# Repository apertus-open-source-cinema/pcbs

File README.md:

# apertus pcbs
This generates artefacts (gerbers, etc.) for the eagle based PCBs of the apertus project. 
Currently it generates
- a zip with gerbers for the [4 layer oshpark process](https://docs.oshpark.com/services/four-layer/)
- (searchable) PDFs of the schematic
- preview images of the boards
- a [webpage](https://apertus-open-source-cinema.github.io/pcbs) that displays these artefacts grouped by board versions and variants
## Process
Generating these artefacts is a multi step process. First the board and schematic files located in the `boards` folder are analyzed to determine license and copyright information from the silkscreen and schematic annotations. This will generate `.license` files for each board and schematic file that does not already have one. To run this steps use 
```sh
python3 analyze.py
```
Please check the extracted information for correctness and fix any errors found before commiting the `.license` file.

The next step of the process is the collection of all the PCB versions, variants and assembly variants. This is done by running
``` sh
python3 generate_info.py
```
This creates `info.json` containing all the infos.

Now the gerbers, schematic PDFs and preview images are generated. For this step EAGLE version 7 needs to be installed. Running
``` sh
python3 gen.py
```
will then generate them. This can take very long depending on the number of cpu cores.

Finally the webpage displaying and providing download links can be generated. For this the preview first images need to be converted from PNG to WebP. This can for example be done with

``` sh
find boards -name '*.png' | parallel -j100% cwebp -lossless {} -o {.}.webp
```

Then the webpage can be built:
``` sh
cd web && npm run build
```
Note that this will generate a webpage for deployment at https://apertus-open-source-cinema.github.io/pcbs/. For local development you can use
``` sh
cd web && npm install && parcel serve src/index.html
```
## CI setup
The CI does almost the same steps as described above. It uses a docker container generated using
``` sh
$(nix-build --no-out-link docker_image.nix) | docker load
```
to run the steps depending on eagle and furthermore uses `xvfb-run` to avoid the need of an actual X11 server.

Finally it splits the `gen.py` step into multiple shards that are run in parallel across multiple workers, as a single worker can not finish under the `6h` time limit.
## Adding PCBs
To add a new PCB simply drop the pair of `.sch` and `.brd` files in the `boards` folder followed by running 
```sh 
python analyze.py
```
and fixing / manually adding the `.license` files.

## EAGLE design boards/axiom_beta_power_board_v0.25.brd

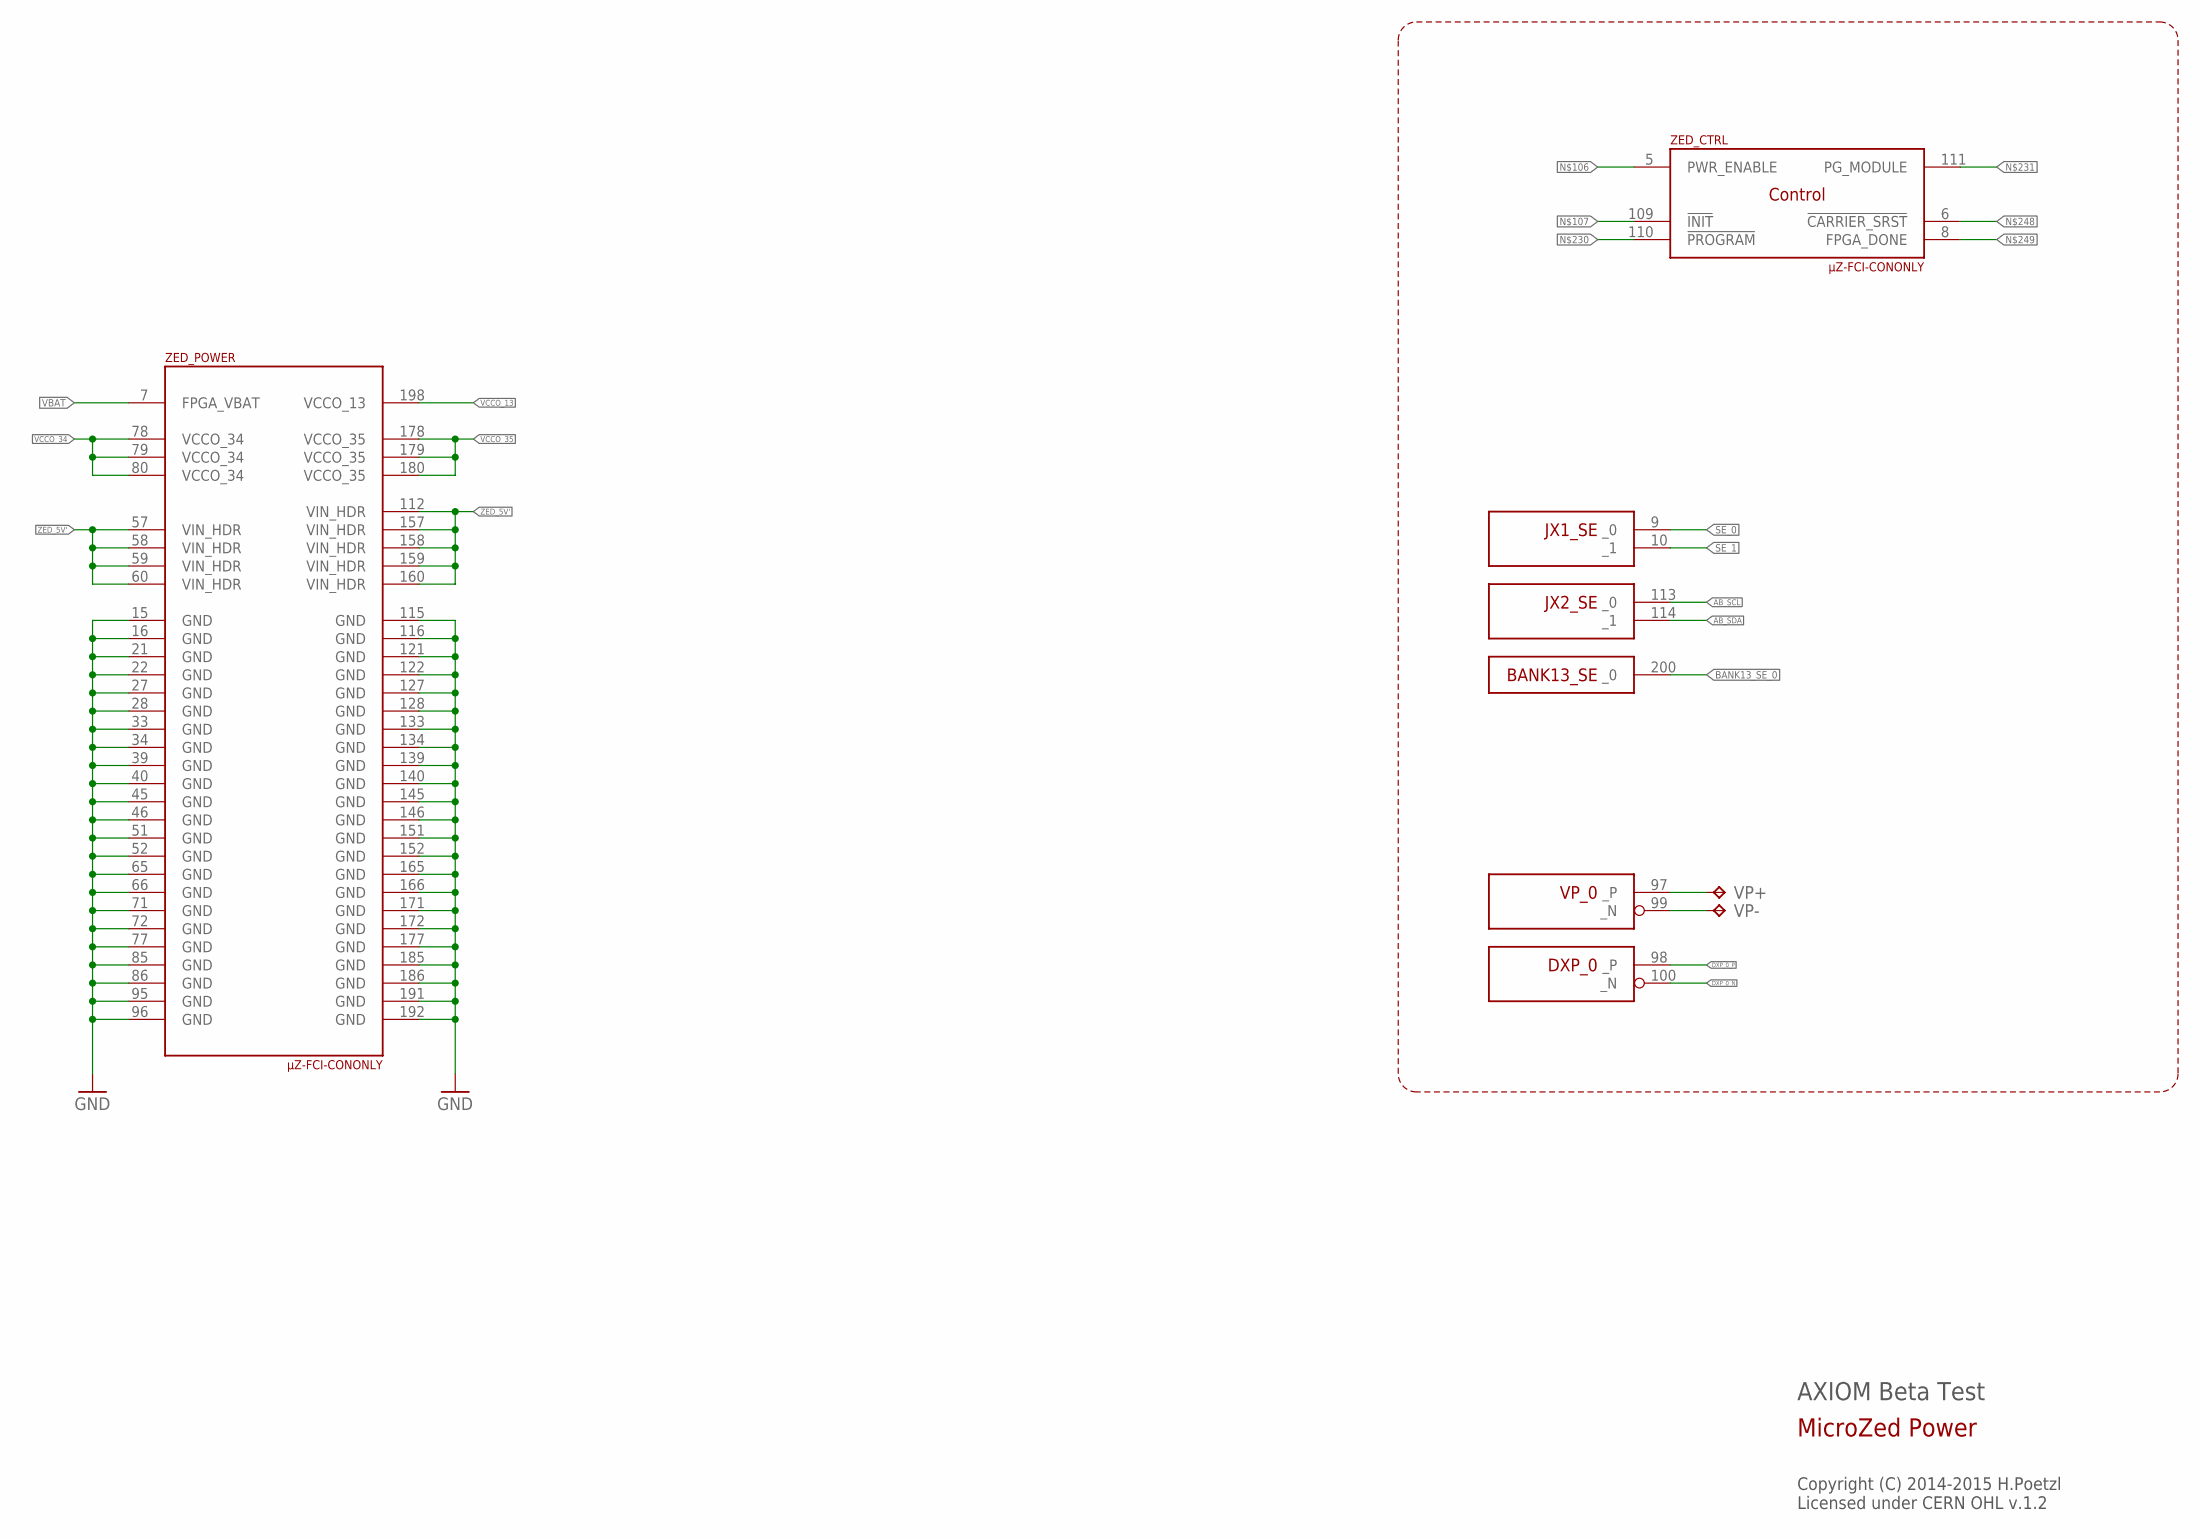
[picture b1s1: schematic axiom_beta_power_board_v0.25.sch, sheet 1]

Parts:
VP+: TPTP16SQ; TP16SQ
VP-: TPTP16SQ; TP16SQ
ZED: µZ-FCI-CONONLY; µZ-CONONLY

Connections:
AB_SCL: ZED.113 (_0); also elsewhere on the board
AB_SDA: ZED.114 (_1); also elsewhere on the board
BANK13_SE_0: ZED.200 (_0); also elsewhere on the board
DXP_0_N: ZED.100 (_N)
DXP_0_P: ZED.98 (_P)
GND: ZED.15 (GND), ZED.16 (GND), ZED.21 (GND), ZED.22 (GND), ZED.27 (GND), ZED.28 (GND), ZED.33 (GND), ZED.34 (GND), ZED.39 (GND), ZED.40 (GND), ZED.45 (GND), ZED.46 (GND), ZED.51 (GND), ZED.52 (GND), ZED.65 (GND), ZED.66 (GND), ZED.71 (GND), ZED.72 (GND), ZED.77 (GND), ZED.85 (GND), ZED.86 (GND), ZED.95 (GND), ZED.96 (GND), ZED.115 (GND), ZED.116 (GND), ZED.121 (GND), ZED.122 (GND), ZED.127 (GND), ZED.128 (GND), ZED.133 (GND), ZED.134 (GND), ZED.139 (GND), ZED.140 (GND), ZED.145 (GND), ZED.146 (GND), ZED.151 (GND), ZED.152 (GND), ZED.165 (GND), ZED.166 (GND), ZED.171 (GND), ZED.172 (GND), ZED.177 (GND), ZED.185 (GND), ZED.186 (GND), ZED.191 (GND), ZED.192 (GND); also elsewhere on the board
SE_0: ZED.9 (_0); also elsewhere on the board
SE_1: ZED.10 (_1); also elsewhere on the board
VBAT: ZED.7 (FPGA_VBAT)
VCCO_13: ZED.198 (VCCO_13); also elsewhere on the board
VCCO_34: ZED.78 (VCCO_34), ZED.79 (VCCO_34), ZED.80 (VCCO_34); also elsewhere on the board
VCCO_35: ZED.178 (VCCO_35), ZED.179 (VCCO_35), ZED.180 (VCCO_35); also elsewhere on the board
VP_0_N: VP-.TP, ZED.99 (_N)
VP_0_P: VP+.TP, ZED.97 (_P)
ZED_5V': ZED.57 (VIN_HDR), ZED.58 (VIN_HDR), ZED.59 (VIN_HDR), ZED.60 (VIN_HDR), ZED.112 (VIN_HDR), ZED.157 (VIN_HDR), ZED.158 (VIN_HDR), ZED.159 (VIN_HDR), ZED.160 (VIN_HDR); also elsewhere on the board

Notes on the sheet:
AXIOM Beta Test
Copyright (C) 2014-2015 H.Poetzl Licensed under CERN OHL v.1.2
MicroZed Power

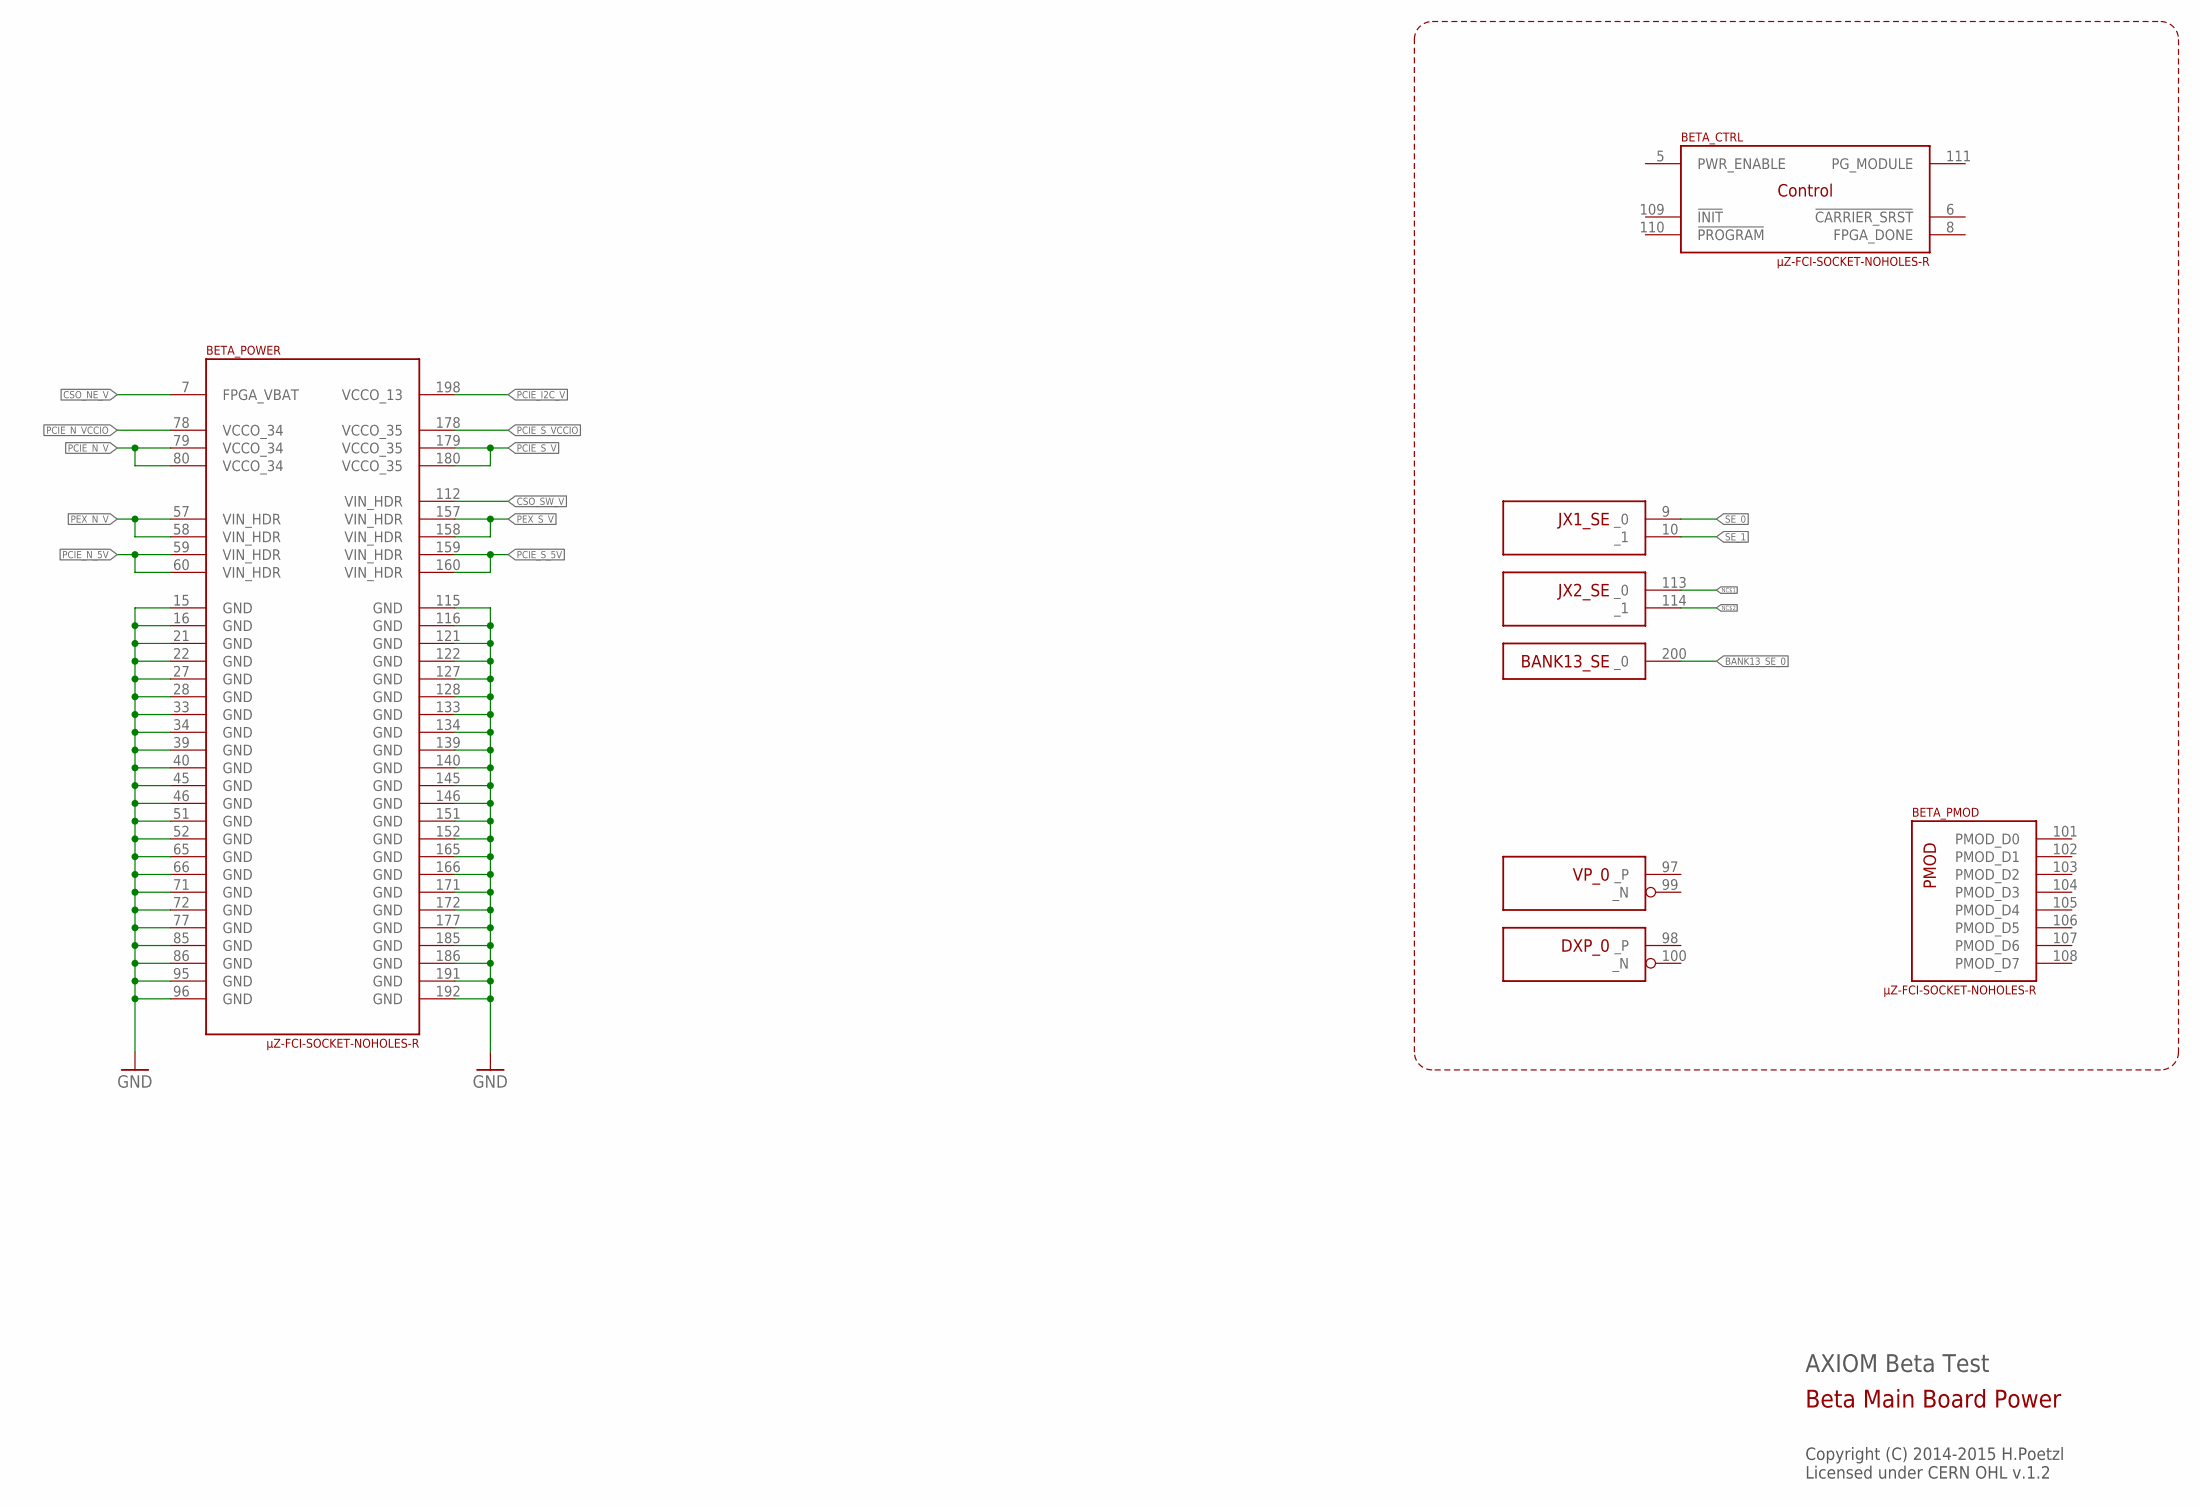
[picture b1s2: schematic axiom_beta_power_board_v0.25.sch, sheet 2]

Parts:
BETA: µZ-FCI-SOCKET-NOHOLES-R; µZ-SOCKET-NOHOLES-R

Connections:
BANK13_SE_0: BETA.200 (_0); also elsewhere on the board
CSO_NE_V: BETA.7 (FPGA_VBAT); also elsewhere on the board
CSO_SW_V: BETA.112 (VIN_HDR); also elsewhere on the board
GND: BETA.15 (GND), BETA.16 (GND), BETA.21 (GND), BETA.22 (GND), BETA.27 (GND), BETA.28 (GND), BETA.33 (GND), BETA.34 (GND), BETA.39 (GND), BETA.40 (GND), BETA.45 (GND), BETA.46 (GND), BETA.51 (GND), BETA.52 (GND), BETA.65 (GND), BETA.66 (GND), BETA.71 (GND), BETA.72 (GND), BETA.77 (GND), BETA.85 (GND), BETA.86 (GND), BETA.95 (GND), BETA.96 (GND), BETA.115 (GND), BETA.116 (GND), BETA.121 (GND), BETA.122 (GND), BETA.127 (GND), BETA.128 (GND), BETA.133 (GND), BETA.134 (GND), BETA.139 (GND), BETA.140 (GND), BETA.145 (GND), BETA.146 (GND), BETA.151 (GND), BETA.152 (GND), BETA.165 (GND), BETA.166 (GND), BETA.171 (GND), BETA.172 (GND), BETA.177 (GND), BETA.185 (GND), BETA.186 (GND), BETA.191 (GND), BETA.192 (GND); also elsewhere on the board
NC$1: BETA.113 (_0)
NC$2: BETA.114 (_1)
PCIE_I2C_V: BETA.198 (VCCO_13)
PCIE_N_5V: BETA.59 (VIN_HDR), BETA.60 (VIN_HDR)
PCIE_N_V: BETA.79 (VCCO_34), BETA.80 (VCCO_34); also elsewhere on the board
PCIE_N_VCCIO: BETA.78 (VCCO_34)
PCIE_S_5V: BETA.159 (VIN_HDR), BETA.160 (VIN_HDR)
PCIE_S_V: BETA.179 (VCCO_35), BETA.180 (VCCO_35); also elsewhere on the board
PCIE_S_VCCIO: BETA.178 (VCCO_35)
PEX_N_V: BETA.57 (VIN_HDR), BETA.58 (VIN_HDR)
PEX_S_V: BETA.157 (VIN_HDR), BETA.158 (VIN_HDR)
SE_0: BETA.9 (_0); also elsewhere on the board
SE_1: BETA.10 (_1); also elsewhere on the board

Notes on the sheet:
AXIOM Beta Test
Copyright (C) 2014-2015 H.Poetzl Licensed under CERN OHL v.1.2
Beta Main Board Power

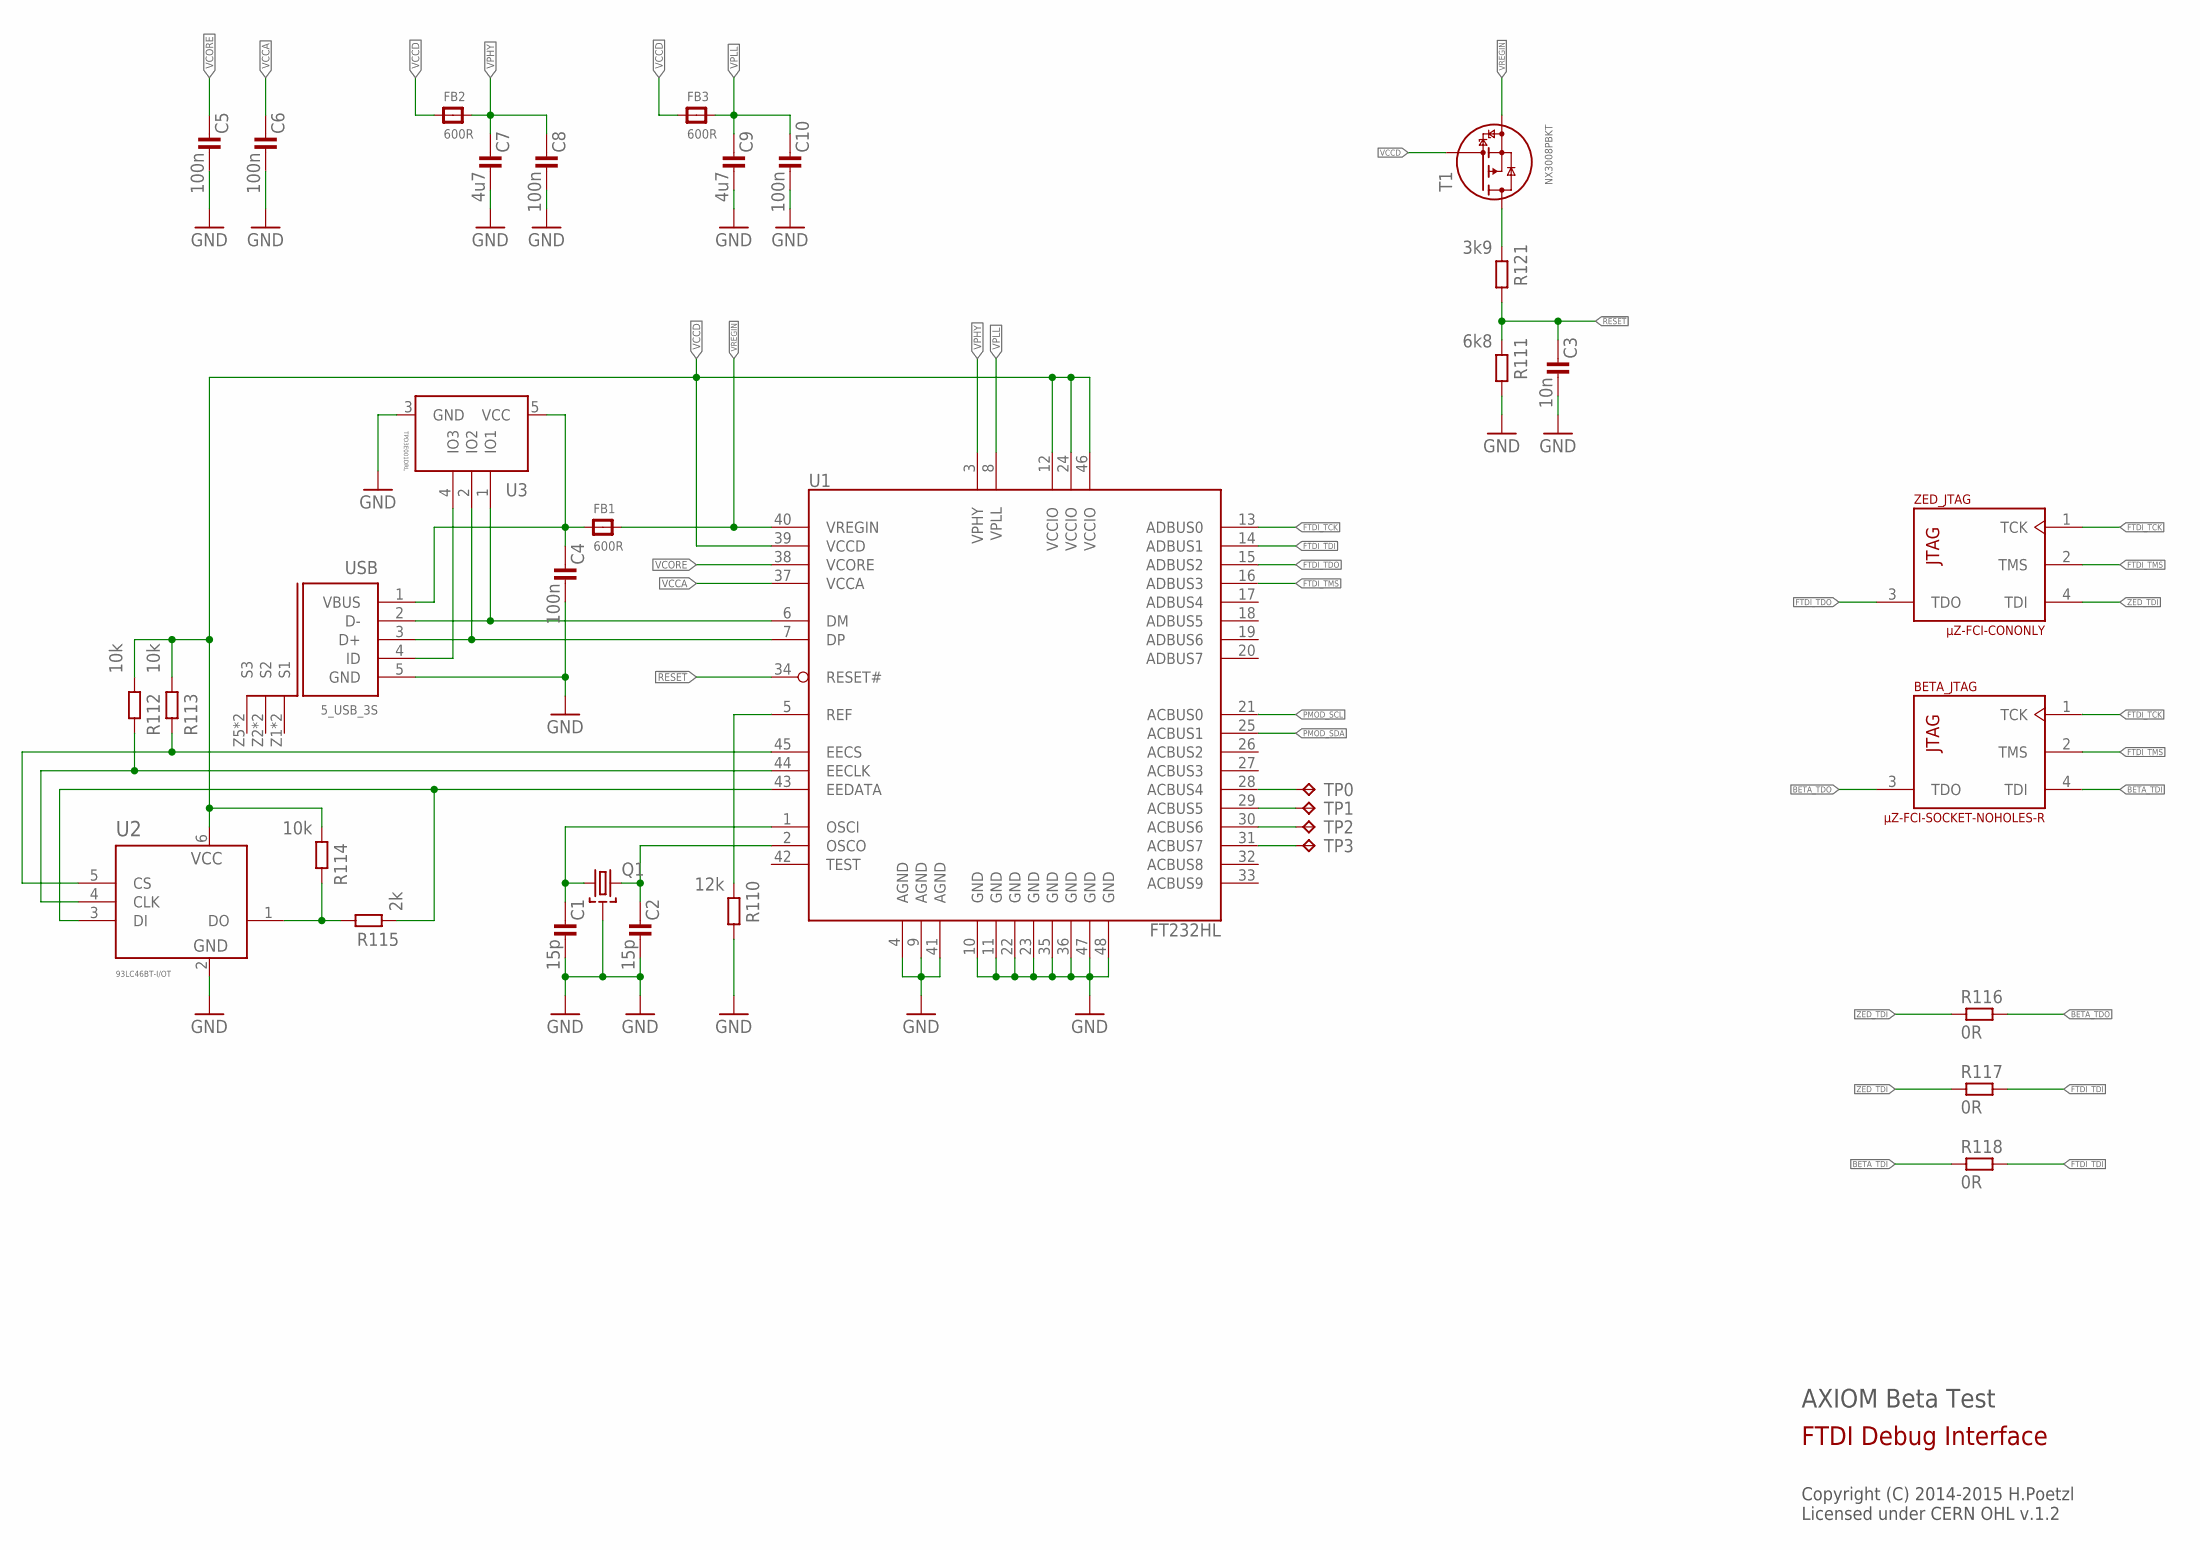
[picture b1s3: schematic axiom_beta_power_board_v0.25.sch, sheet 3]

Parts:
BETA: µZ-FCI-SOCKET-NOHOLES-R; µZ-SOCKET-NOHOLES-R
C1, C2: 15p; 0402-B
C3: 10n; 0402-B
C4: 100n; 0603-B
C5, C6, C8, C10: 100n; 0402-B
C7, C9: 4u7; 0603-B
FB1, FB2, FB3: 600R; _0603MP
Q1: SMD-4P-2G-3.2X2.5; ABM8G
R110: 12k; 0402-B
R111: 6k8; 0402-B
R112, R113, R114: 10k; 0402-B
R115: 2k; 0402-B
R116, R117, R118: 0R; 0402-B
R121: 3k9; 0402-B
T1: NX3008PBKT; SOT416
TP0, TP1, TP2, TP3: TPTP16SQ; TP16SQ
U1: FT232HL; LQFP48
U2: 93LC46BT-I/OT; SOT95P280X145-6N
U3: TPD3E001DRL; R-PDSO-N5
USB: 5_USB_3S; MICRO-AB-H-SMT
ZED: µZ-FCI-CONONLY; µZ-CONONLY

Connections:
!RESET: C3.1, R111.2, R121.1, U1.34 (RESET#)
BETA_TDI: BETA.4 (TDI), R118.2
BETA_TDO: BETA.3 (TDO), R116.1
EE_CLK1: R112.1, U1.44 (EECLK), U2.4 (CLK)
EE_CS1: R113.1, U1.45 (EECS), U2.5 (CS)
EE_DATA1: R115.2, U1.43 (EEDATA), U2.3 (DI)
FTDI_D_N: U1.6 (DM), U3.1 (IO1), USB.2 (D-)
FTDI_D_P: U1.7 (DP), U3.2 (IO2), USB.3 (D+)
FTDI_TCK: BETA.1 (TCK), U1.13 (ADBUS0), ZED.1 (TCK)
FTDI_TDI: R117.1, R118.1, U1.14 (ADBUS1)
FTDI_TDO: U1.15 (ADBUS2), ZED.3 (TDO)
FTDI_TMS: BETA.2 (TMS), U1.16 (ADBUS3), ZED.2 (TMS)
GND: C1.2, C2.2, C3.2, C4.2, C5.2, C6.2, C7.2, C8.2, C9.2, C10.2, Q1.2 (GND), Q1.4 (GND), R110.1, R111.1, U1.4 (AGND), U1.9 (AGND), U1.10 (GND), U1.11 (GND), U1.22 (GND), U1.23 (GND), U1.35 (GND), U1.36 (GND), U1.41 (AGND), U1.47 (GND), U1.48 (GND), U2.2 (VSS), U3.3 (GND), USB.5 (GND); also elsewhere on the board
unnamed: C4.1, FB1.1, U3.5 (VCC), USB.1 (VBUS)
unnamed: R121.2, T1.3 (D)
unnamed: TP0.TP, U1.28 (ACBUS4)
unnamed: TP1.TP, U1.29 (ACBUS5)
unnamed: TP2.TP, U1.30 (ACBUS6)
unnamed: TP3.TP, U1.31 (ACBUS7)
unnamed: R114.1, R115.1, U2.1 (DO)
unnamed: C1.1, Q1.1, U1.1 (OSCI)
unnamed: C2.1, Q1.3 (2), U1.2 (OSCO)
unnamed: R110.2, U1.5 (REF)
unnamed: U3.4 (IO3), USB.4 (ID)
PMOD_SCL: U1.21 (ACBUS0); also elsewhere on the board
PMOD_SDA: U1.25 (ACBUS1); also elsewhere on the board
VCCA: C6.1, U1.37 (VCCA)
VCCD: FB2.1, FB3.1, R112.2, R113.2, R114.2, T1.1 (G), U1.12 (VCCIO), U1.24 (VCCIO), U1.39 (VCCD), U1.46 (VCCIO), U2.6 (VCC)
VCORE: C5.1, U1.38 (VCORE)
VPHY: C7.1, C8.1, FB2.2, U1.3 (VPHY)
VPLL: C9.1, C10.1, FB3.2, U1.8 (VPLL)
VREGIN: FB1.2, T1.2 (S), U1.40 (VREGIN)
ZED_TDI: R116.2, R117.2, ZED.4 (TDI)

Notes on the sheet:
AXIOM Beta Test
Copyright (C) 2014-2015 H.Poetzl Licensed under CERN OHL v.1.2
FTDI Debug Interface

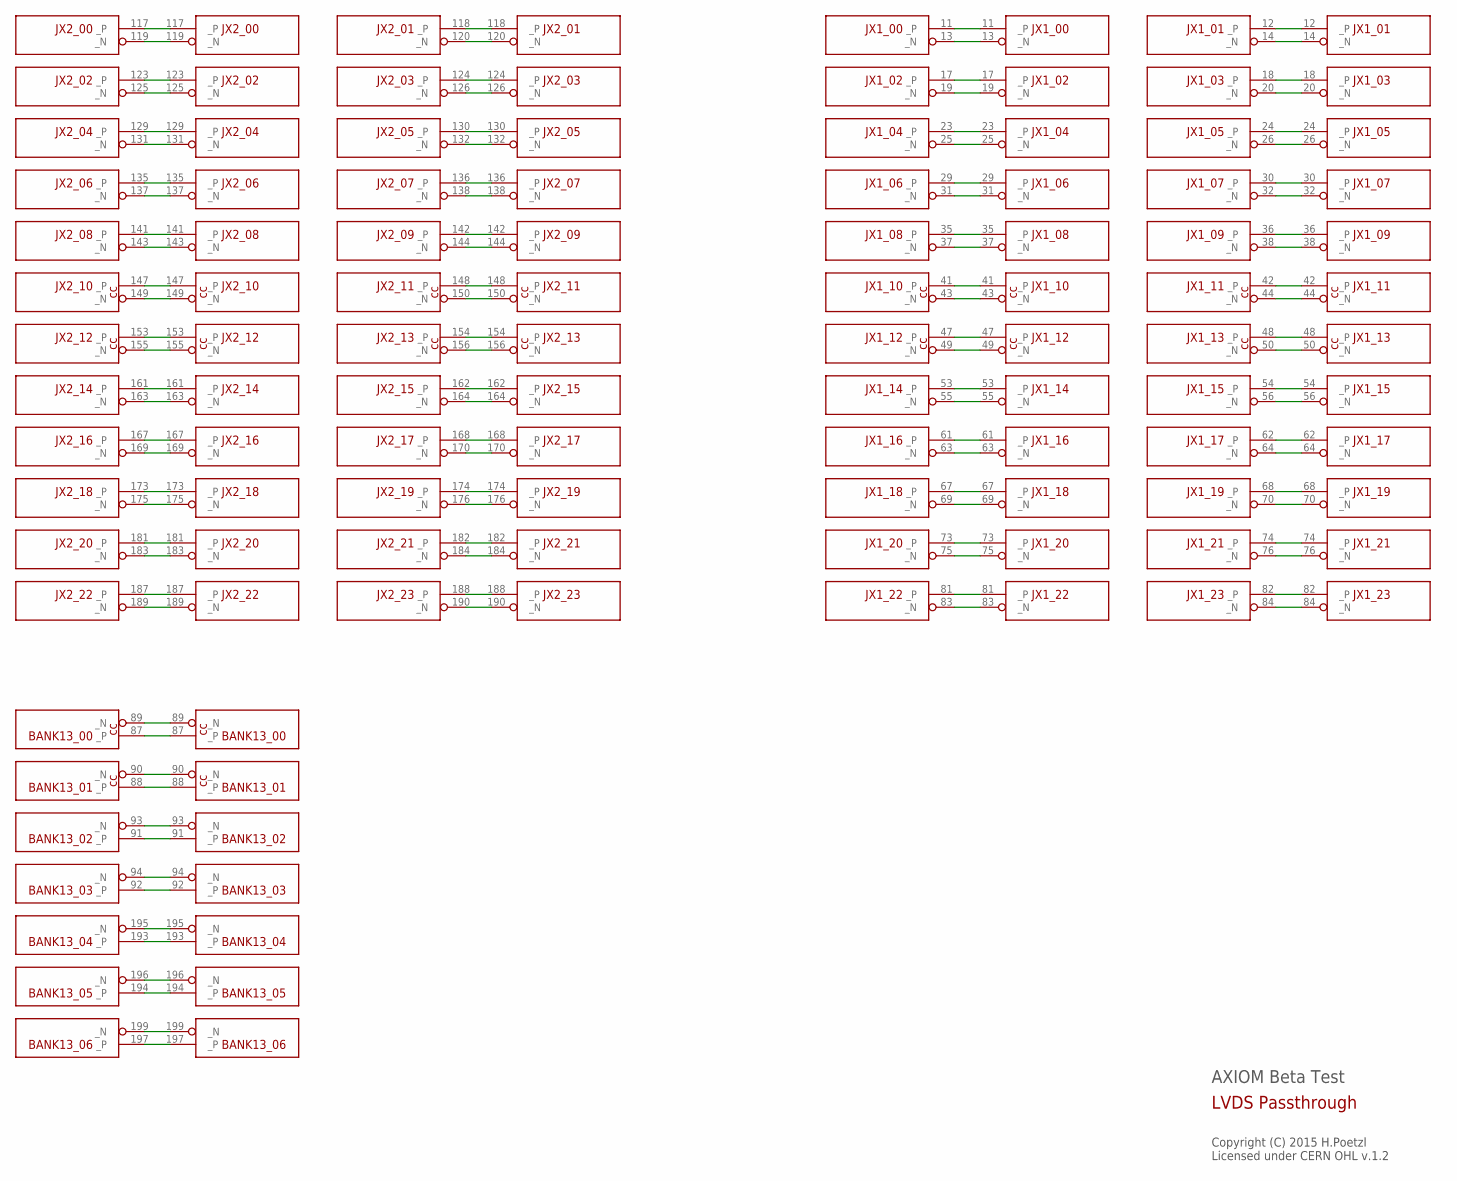
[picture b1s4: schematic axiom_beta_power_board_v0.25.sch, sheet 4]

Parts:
BETA: µZ-FCI-SOCKET-NOHOLES-R; µZ-SOCKET-NOHOLES-R
ZED: µZ-FCI-CONONLY; µZ-CONONLY

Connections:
BANK13_00_N: BETA.89 (_N), ZED.89 (_N)
BANK13_00_P: BETA.87 (_P), ZED.87 (_P)
BANK13_01_N: BETA.90 (_N), ZED.90 (_N)
BANK13_01_P: BETA.88 (_P), ZED.88 (_P)
BANK13_02_N: BETA.93 (_N), ZED.93 (_N)
BANK13_02_P: BETA.91 (_P), ZED.91 (_P)
BANK13_03_N: BETA.94 (_N), ZED.94 (_N)
BANK13_03_P: BETA.92 (_P), ZED.92 (_P)
BANK13_04_N: BETA.195 (_N), ZED.195 (_N)
BANK13_04_P: BETA.193 (_P), ZED.193 (_P)
BANK13_05_N: BETA.196 (_N), ZED.196 (_N)
BANK13_05_P: BETA.194 (_P), ZED.194 (_P)
BANK13_06_N: BETA.199 (_N), ZED.199 (_N)
BANK13_06_P: BETA.197 (_P), ZED.197 (_P)
JX1_00_N: BETA.13 (_N), ZED.13 (_N)
JX1_00_P: BETA.11 (_P), ZED.11 (_P)
JX1_01_N: BETA.14 (_N), ZED.14 (_N)
JX1_01_P: BETA.12 (_P), ZED.12 (_P)
JX1_02_N: BETA.19 (_N), ZED.19 (_N)
JX1_02_P: BETA.17 (_P), ZED.17 (_P)
JX1_03_N: BETA.20 (_N), ZED.20 (_N)
JX1_03_P: BETA.18 (_P), ZED.18 (_P)
JX1_04_N: BETA.25 (_N), ZED.25 (_N)
JX1_04_P: BETA.23 (_P), ZED.23 (_P)
JX1_05_N: BETA.26 (_N), ZED.26 (_N)
JX1_05_P: BETA.24 (_P), ZED.24 (_P)
JX1_06_N: BETA.31 (_N), ZED.31 (_N)
JX1_06_P: BETA.29 (_P), ZED.29 (_P)
JX1_07_N: BETA.32 (_N), ZED.32 (_N)
JX1_07_P: BETA.30 (_P), ZED.30 (_P)
JX1_08_N: BETA.37 (_N), ZED.37 (_N)
JX1_08_P: BETA.35 (_P), ZED.35 (_P)
JX1_09_N: BETA.38 (_N), ZED.38 (_N)
JX1_09_P: BETA.36 (_P), ZED.36 (_P)
JX1_10_N: BETA.43 (_N), ZED.43 (_N)
JX1_10_P: BETA.41 (_P), ZED.41 (_P)
JX1_11_N: BETA.44 (_N), ZED.44 (_N)
JX1_11_P: BETA.42 (_P), ZED.42 (_P)
JX1_12_N: BETA.49 (_N), ZED.49 (_N)
JX1_12_P: BETA.47 (_P), ZED.47 (_P)
JX1_13_N: BETA.50 (_N), ZED.50 (_N)
JX1_13_P: BETA.48 (_P), ZED.48 (_P)
JX1_14_N: BETA.55 (_N), ZED.55 (_N)
JX1_14_P: BETA.53 (_P), ZED.53 (_P)
JX1_15_N: BETA.56 (_N), ZED.56 (_N)
JX1_15_P: BETA.54 (_P), ZED.54 (_P)
JX1_16_N: BETA.63 (_N), ZED.63 (_N)
JX1_16_P: BETA.61 (_P), ZED.61 (_P)
JX1_17_N: BETA.64 (_N), ZED.64 (_N)
JX1_17_P: BETA.62 (_P), ZED.62 (_P)
JX1_18_N: BETA.69 (_N), ZED.69 (_N)
JX1_18_P: BETA.67 (_P), ZED.67 (_P)
JX1_19_N: BETA.70 (_N), ZED.70 (_N)
JX1_19_P: BETA.68 (_P), ZED.68 (_P)
JX1_20_N: BETA.75 (_N), ZED.75 (_N)
JX1_20_P: BETA.73 (_P), ZED.73 (_P)
JX1_21_N: BETA.76 (_N), ZED.76 (_N)
JX1_21_P: BETA.74 (_P), ZED.74 (_P)
JX1_22_N: BETA.83 (_N), ZED.83 (_N)
JX1_22_P: BETA.81 (_P), ZED.81 (_P)
JX1_23_N: BETA.84 (_N), ZED.84 (_N)
JX1_23_P: BETA.82 (_P), ZED.82 (_P)
JX2_00_N: BETA.119 (_N), ZED.119 (_N)
JX2_00_P: BETA.117 (_P), ZED.117 (_P)
JX2_01_N: BETA.120 (_N), ZED.120 (_N)
JX2_01_P: BETA.118 (_P), ZED.118 (_P)
JX2_02_N: BETA.125 (_N), ZED.125 (_N)
JX2_02_P: BETA.123 (_P), ZED.123 (_P)
JX2_03_N: BETA.126 (_N), ZED.126 (_N)
JX2_03_P: BETA.124 (_P), ZED.124 (_P)
JX2_04_N: BETA.131 (_N), ZED.131 (_N)
JX2_04_P: BETA.129 (_P), ZED.129 (_P)
JX2_05_N: BETA.132 (_N), ZED.132 (_N)
JX2_05_P: BETA.130 (_P), ZED.130 (_P)
JX2_06_N: BETA.137 (_N), ZED.137 (_N)
JX2_06_P: BETA.135 (_P), ZED.135 (_P)
JX2_07_N: BETA.138 (_N), ZED.138 (_N)
JX2_07_P: BETA.136 (_P), ZED.136 (_P)
JX2_08_N: BETA.143 (_N), ZED.143 (_N)
JX2_08_P: BETA.141 (_P), ZED.141 (_P)
JX2_09_N: BETA.144 (_N), ZED.144 (_N)
JX2_09_P: BETA.142 (_P), ZED.142 (_P)
JX2_10_N: BETA.149 (_N), ZED.149 (_N)
JX2_10_P: BETA.147 (_P), ZED.147 (_P)
JX2_11_N: BETA.150 (_N), ZED.150 (_N)
JX2_11_P: BETA.148 (_P), ZED.148 (_P)
JX2_12_N: BETA.155 (_N), ZED.155 (_N)
JX2_12_P: BETA.153 (_P), ZED.153 (_P)
JX2_13_N: BETA.156 (_N), ZED.156 (_N)
JX2_13_P: BETA.154 (_P), ZED.154 (_P)
JX2_14_N: BETA.163 (_N), ZED.163 (_N)
JX2_14_P: BETA.161 (_P), ZED.161 (_P)
JX2_15_N: BETA.164 (_N), ZED.164 (_N)
JX2_15_P: BETA.162 (_P), ZED.162 (_P)
JX2_16_N: BETA.169 (_N), ZED.169 (_N)
JX2_16_P: BETA.167 (_P), ZED.167 (_P)
JX2_17_N: BETA.170 (_N), ZED.170 (_N)
JX2_17_P: BETA.168 (_P), ZED.168 (_P)
JX2_18_N: BETA.175 (_N), ZED.175 (_N)
JX2_18_P: BETA.173 (_P), ZED.173 (_P)
JX2_19_N: BETA.176 (_N), ZED.176 (_N)
JX2_19_P: BETA.174 (_P), ZED.174 (_P)
JX2_20_N: BETA.183 (_N), ZED.183 (_N)
JX2_20_P: BETA.181 (_P), ZED.181 (_P)
JX2_21_N: BETA.184 (_N), ZED.184 (_N)
JX2_21_P: BETA.182 (_P), ZED.182 (_P)
JX2_22_N: BETA.189 (_N), ZED.189 (_N)
JX2_22_P: BETA.187 (_P), ZED.187 (_P)
JX2_23_N: BETA.190 (_N), ZED.190 (_N)
JX2_23_P: BETA.188 (_P), ZED.188 (_P)

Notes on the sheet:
AXIOM Beta Test
Copyright (C) 2015 H.Poetzl Licensed under CERN OHL v.1.2
LVDS Passthrough

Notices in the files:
boards/axiom_beta_interface_dummy_v0.9.brd:
Copyright (C) 2015 Herbert Pötzl
boards/axiom_beta_plugin_module_3xmDP_v1.1.brd:
Copyright (C) 2016 Herbert Pötzl
parts and their libraries:
microbuilder: This work is placed in the public domain, and may be freely used for commercial and non-commercial work with the following conditions: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
